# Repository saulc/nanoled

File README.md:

# nanoled
led addon board for nano remote v.2

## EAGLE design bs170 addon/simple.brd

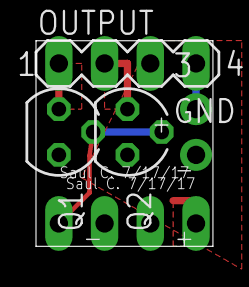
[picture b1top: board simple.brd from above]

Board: 2 copper layers, 9.8 x 11.4 mm, 6 parts (1 on the bottom side), 6 nets.

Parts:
3: 1X01-CLEANBIG
GND: 1X01-CLEANBIG
INPUT: MA04-1
OUTPUT: MA04-1
Q1, Q2: BS170; SOT54E

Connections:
1OUT: OUTPUT.1, Q1.D
2OUT: OUTPUT.2, Q2.D
3OUT: 3.1, OUTPUT.4
4IN: INPUT.4, Q1.G, Q2.G
GND: GND.1, INPUT.3, Q1.S, Q2.S
VCC: INPUT.1, OUTPUT.3

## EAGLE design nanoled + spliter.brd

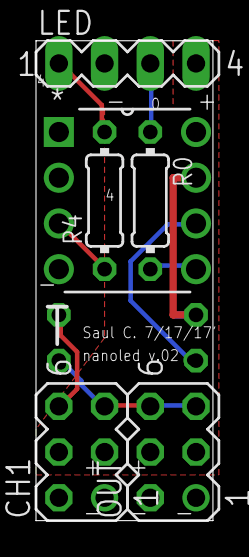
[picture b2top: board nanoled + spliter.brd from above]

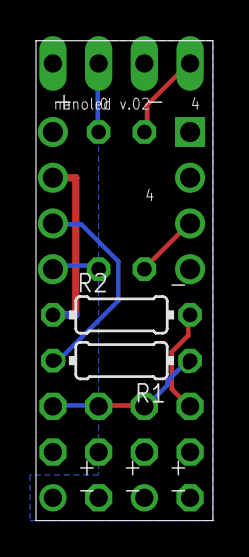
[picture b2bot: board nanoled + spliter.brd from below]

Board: 2 copper layers, 9.8 x 26.7 mm, 8 parts (2 on the bottom side), 10 nets.

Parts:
CH1: MA03-2
LED: MA04-1
OUT: MA03-2
R0, R2: 220; 0204/7
R1: 10k; 0204/7
R4: 0204/7
T: ATTINY85-20PU; DIP254P762X533-8

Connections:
4OUT: LED.1, R4.2
GND: CH1.1, CH1.2, LED.2, OUT.1, OUT.2, T.4
unnamed: LED.3, R0.1
unnamed: CH1.6, R2.2
ONE: CH1.5, OUT.5, OUT.6, R1.1
P0: R0.2, T.5
P1: R1.2, T.6
P2: R2.1, T.7
P4: R4.1, T.3
VCC: CH1.3, CH1.4, LED.4, OUT.4, T.8

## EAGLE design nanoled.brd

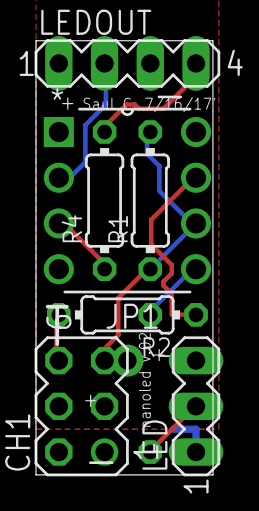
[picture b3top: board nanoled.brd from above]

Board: 2 copper layers, 9.8 x 24.1 mm, 9 parts (1 on the bottom side), 10 nets.

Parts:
CH1: MA03-2
JP1: 1X01-CLEANBIG
LED: MA03-1
LEDOUT: MA04-1
R0, R2: 220; 0204/7
R1: 10k; 0204/7
R4: 0204/7
T: ATTINY85-20PU; DIP254P762X533-8

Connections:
4OUT: LEDOUT.4, R4.2
GND: CH1.1, CH1.2, LED.1, LEDOUT.3, T.4
unnamed: LED.2, R0.1
unnamed: CH1.6, R2.2
P0: R0.2, T.5
P1: CH1.5, JP1.1, R1.1, R1.2, T.6
P2: R2.1, T.7
P3: LEDOUT.2, T.2
P4: R4.1, T.3
VCC: CH1.3, CH1.4, LED.3, LEDOUT.1, T.8

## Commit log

2017-07-17 upload
2017-07-17 addon board
    add for 2x bs170 mostfet (pwm 4) and status led digital3
2017-07-17 add readme
    ..
2017-07-17 add oshpark images
2017-07-17 add image
